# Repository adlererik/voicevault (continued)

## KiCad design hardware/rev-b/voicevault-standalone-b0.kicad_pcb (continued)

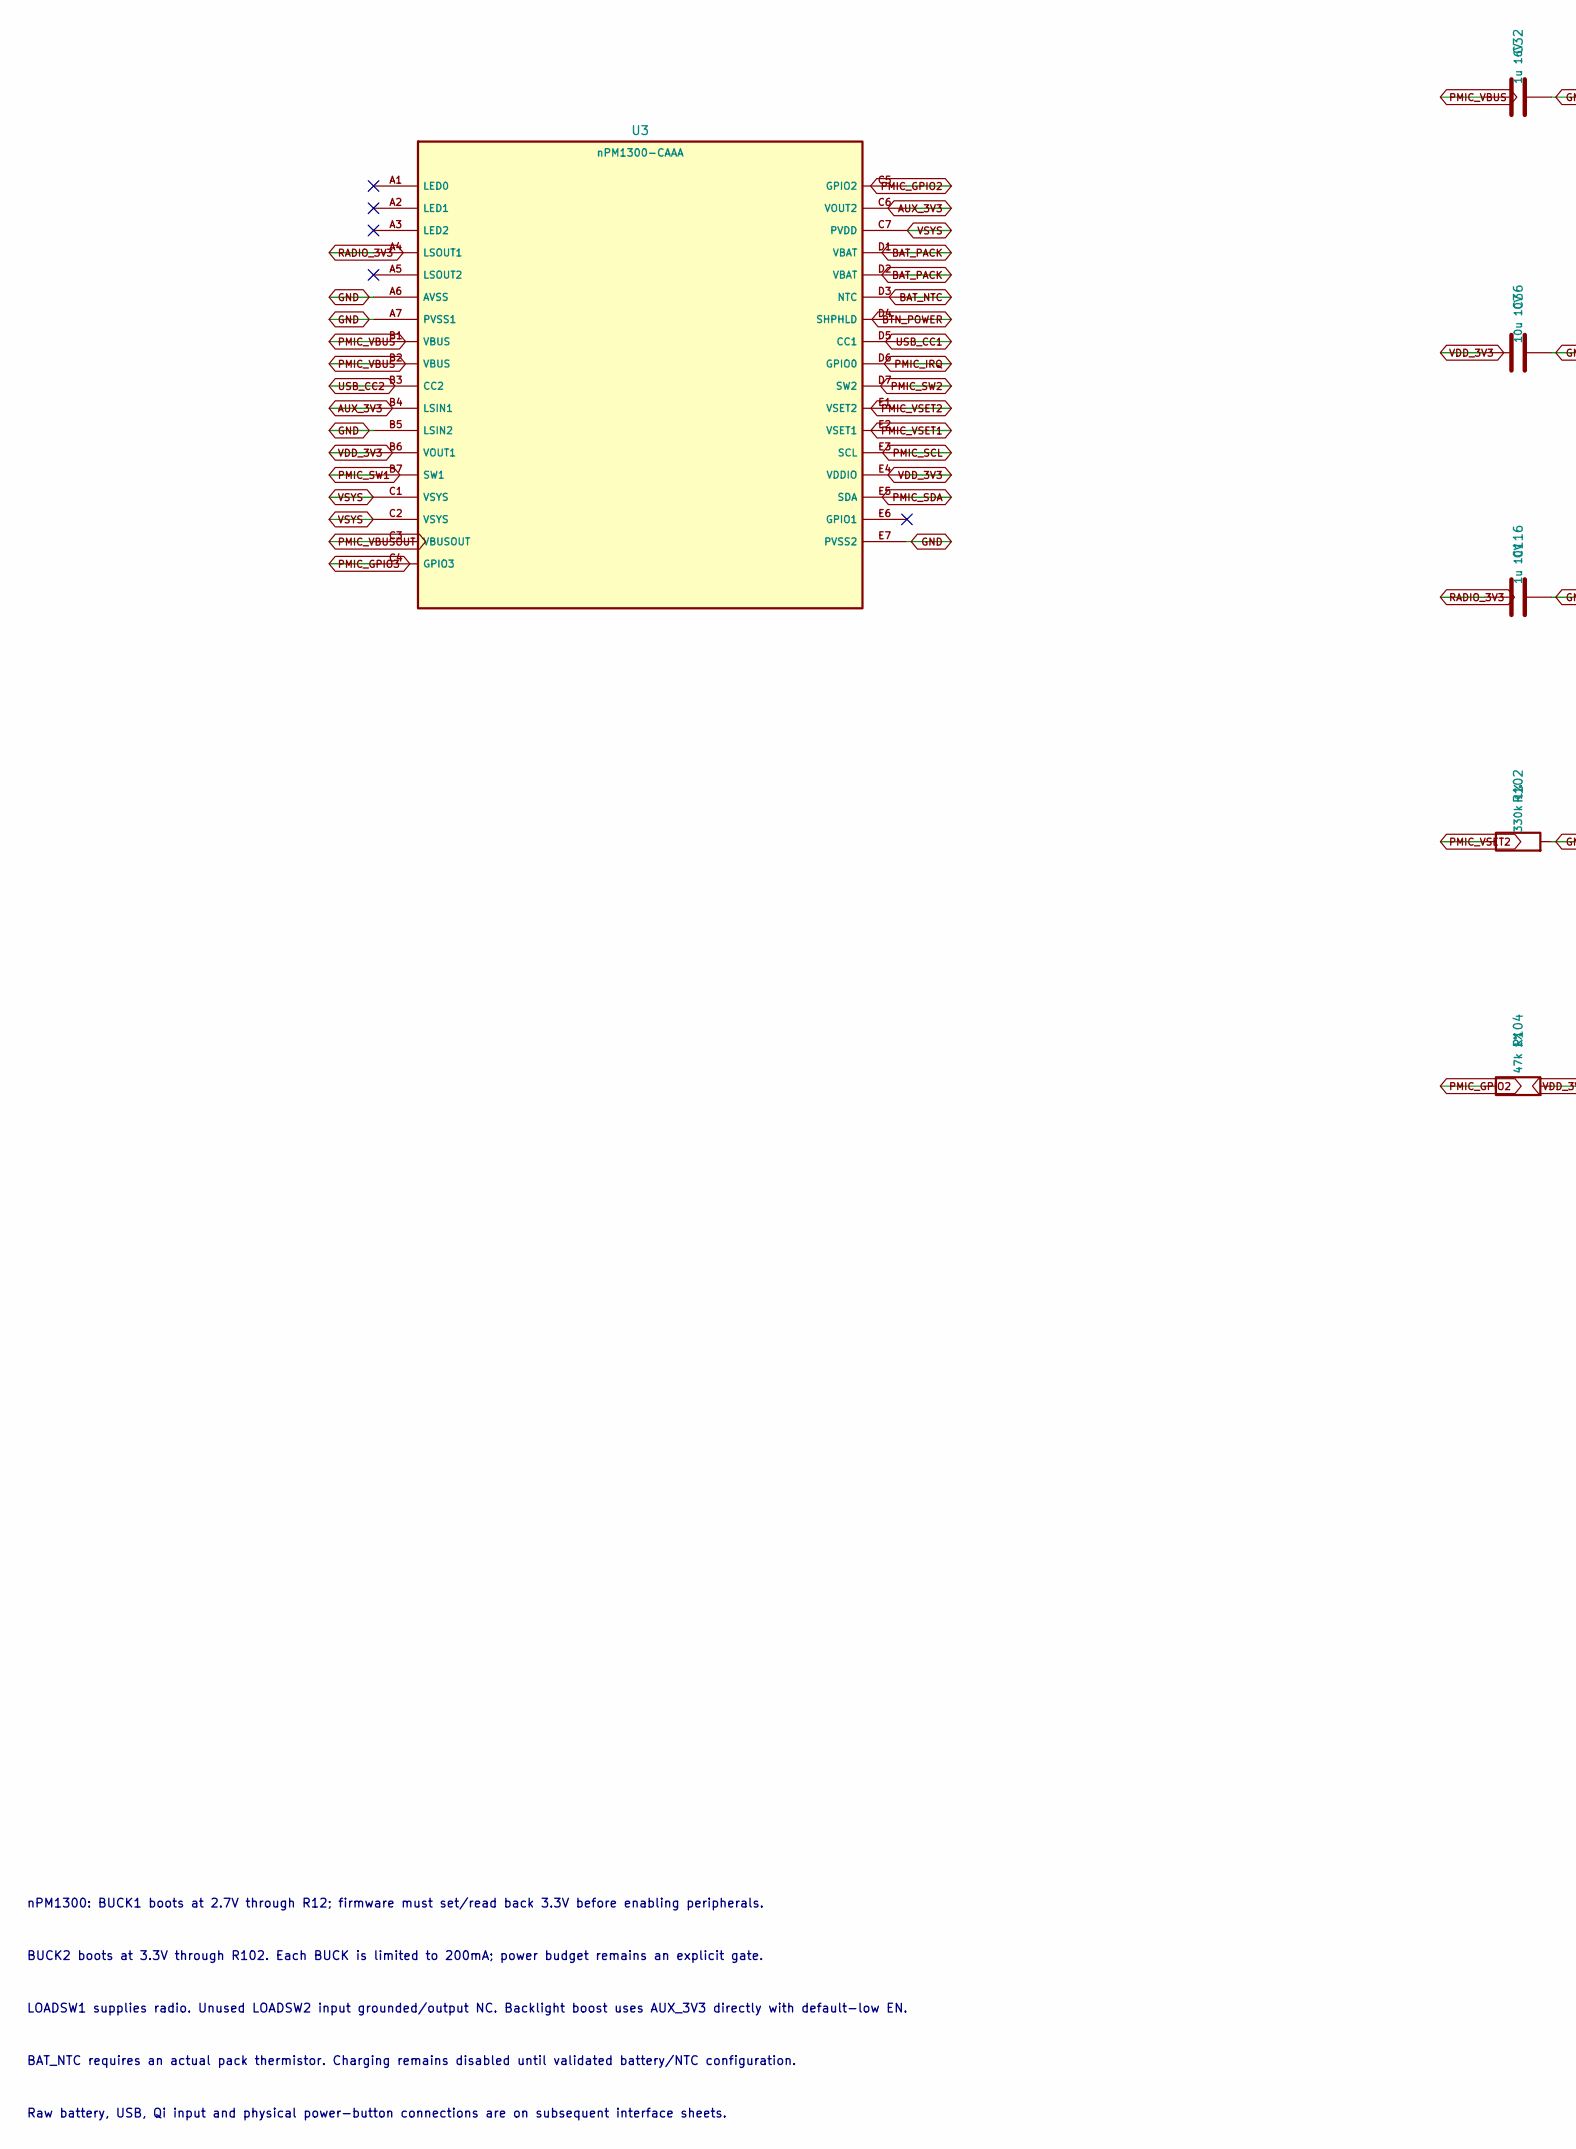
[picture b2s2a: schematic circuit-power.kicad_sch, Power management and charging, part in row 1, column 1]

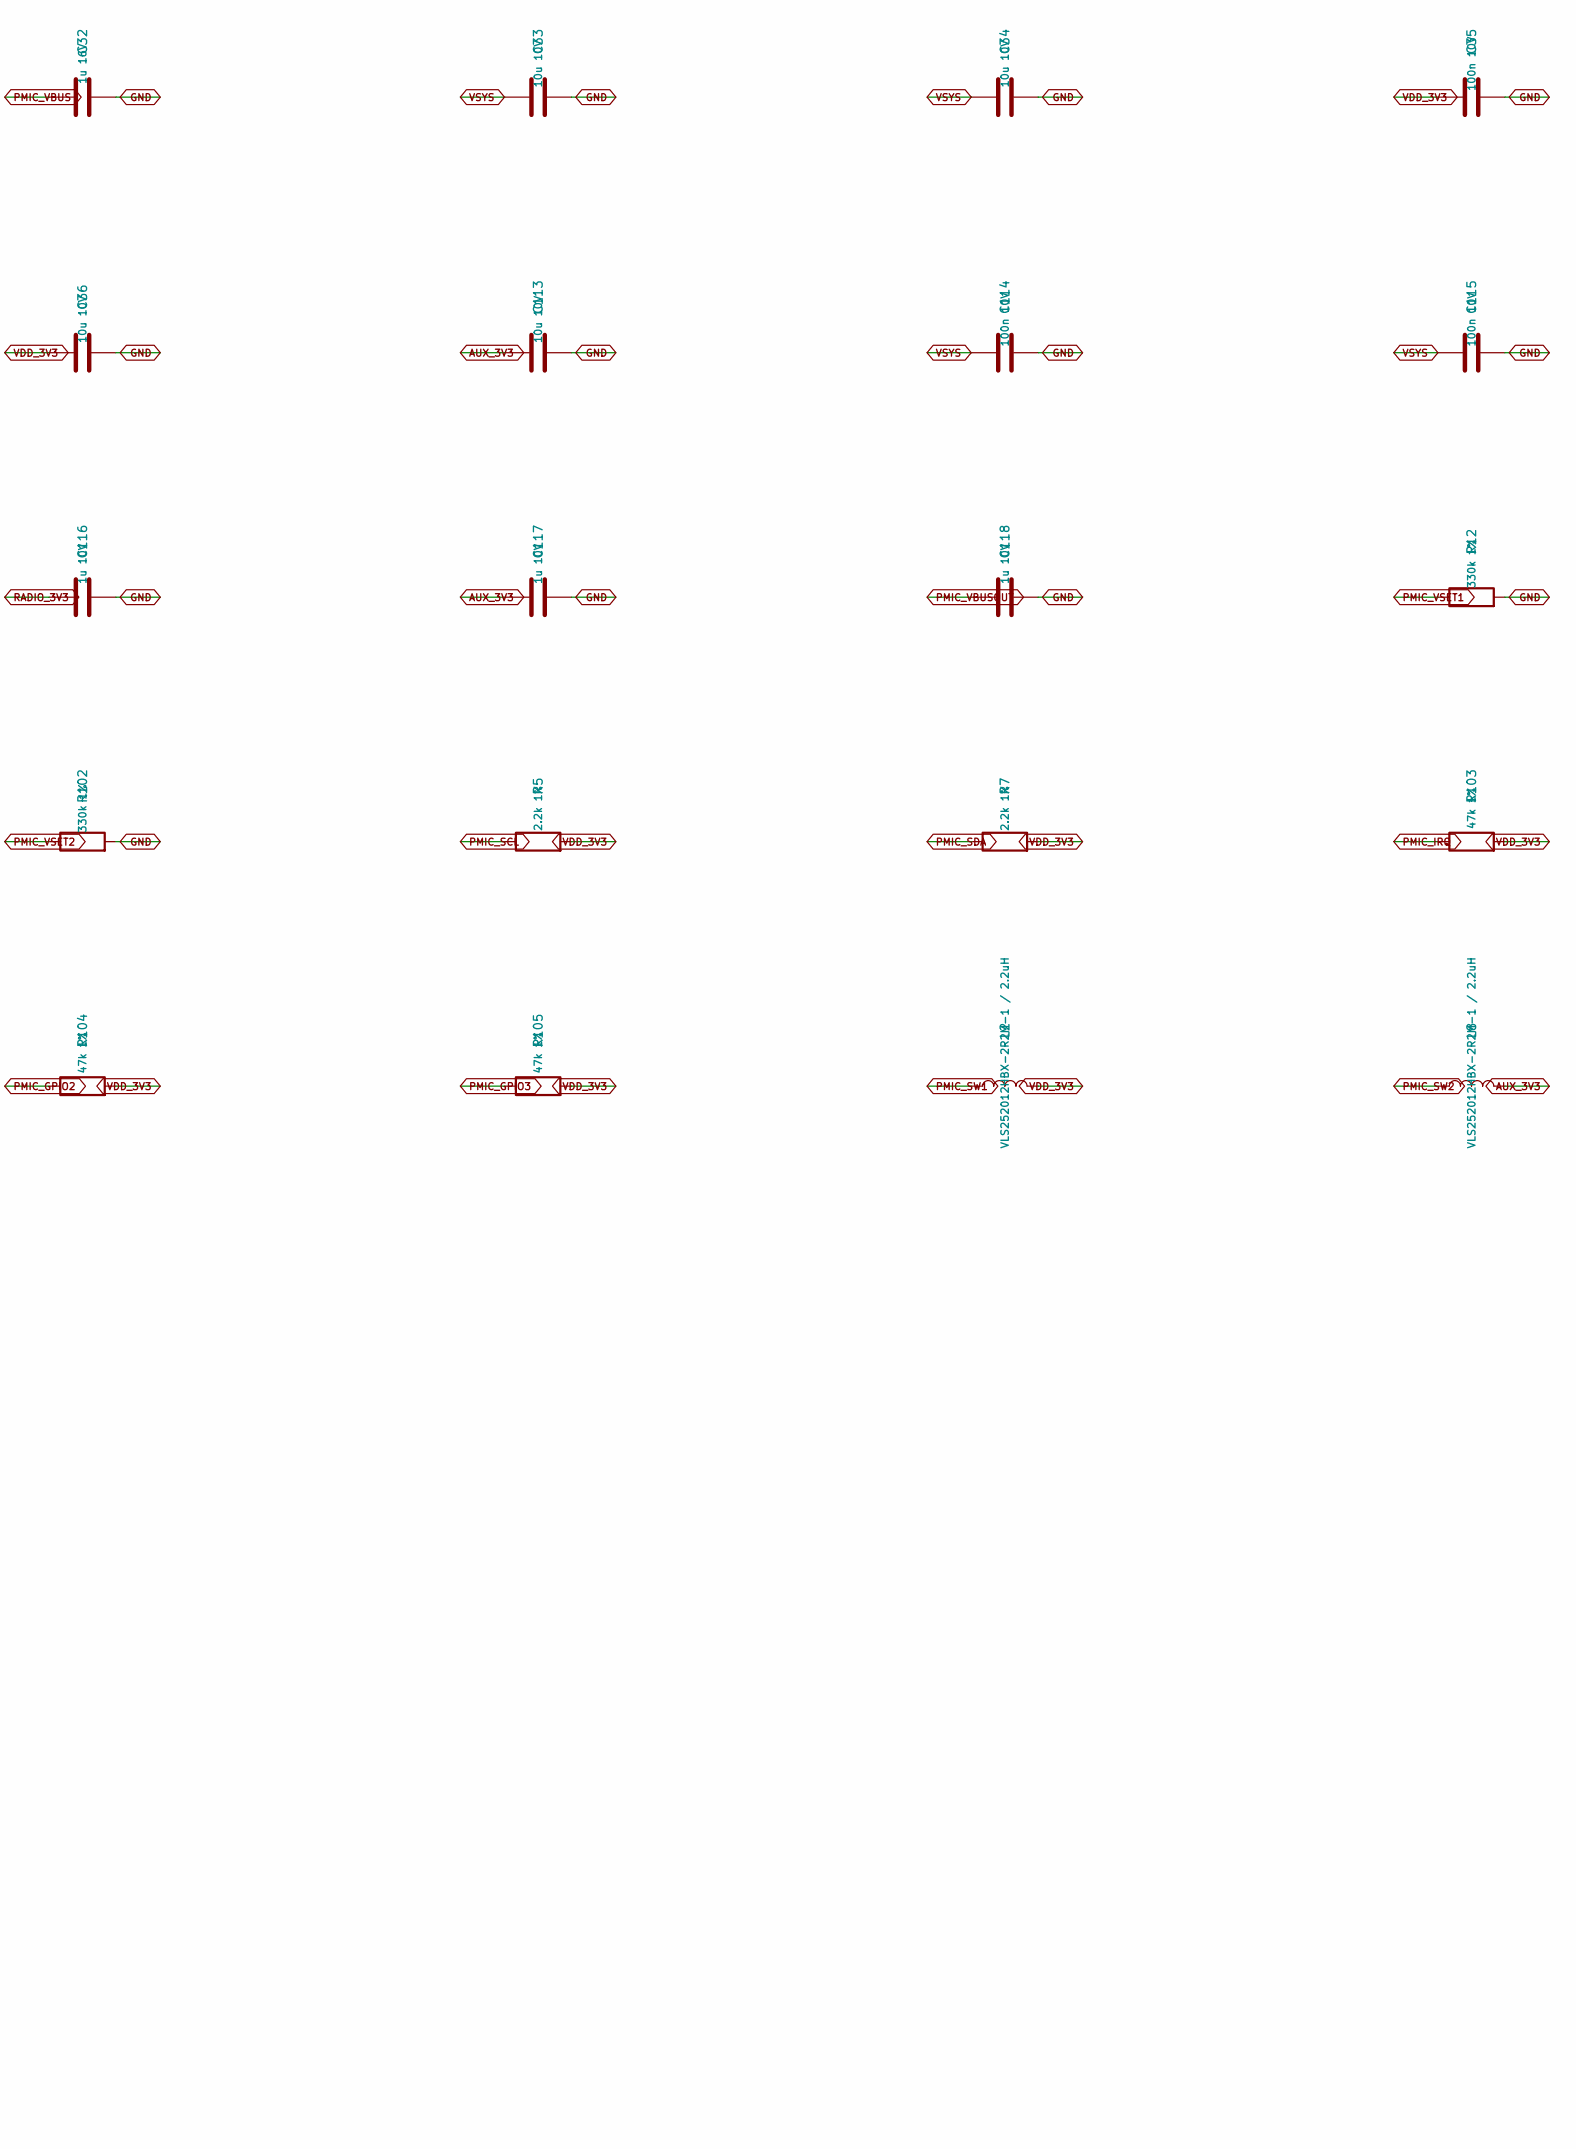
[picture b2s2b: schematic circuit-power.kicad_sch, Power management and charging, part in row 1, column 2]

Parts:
C32: 1u 16V; C_0603_1608Metric
C33, C34, C36, C113: 10u 10V; C_0603_1608Metric
C35, C114, C115: 100n 10V; C_0603_1608Metric
C116, C117, C118: 1u 10V; C_0603_1608Metric
L2, L8: VLS252012HBX-2R2M-1 / 2.2uH; L_1008_2520Metric
R5, R7: 2.2k 1%; R_0402_1005Metric
R12, R102: 330k 1%; R_0402_1005Metric
R103, R104, R105: 47k 1%; R_0402_1005Metric
U3: nPM1300-CAAA; nPM1300_CAAA_Nordic

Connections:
AUX_3V3: C113.1, C117.1, L8.2, U3.B4 (LSIN1), U3.C6 (VOUT2); also elsewhere on the board
BAT_NTC: U3.D3 (NTC); also elsewhere on the board
BAT_PACK: U3.D1 (VBAT), U3.D2 (VBAT); also elsewhere on the board
BTN_POWER: U3.D4 (SHPHLD); also elsewhere on the board
GND: C32.2, C33.2, C34.2, C35.2, C36.2, C113.2, C114.2, C115.2, C116.2, C117.2, C118.2, R12.2, R102.2, U3.A6 (AVSS), U3.A7 (PVSS1), U3.B5 (LSIN2), U3.E7 (PVSS2); also elsewhere on the board
PMIC_GPIO2: R104.1, U3.C5 (GPIO2); also elsewhere on the board
PMIC_GPIO3: R105.1, U3.C4 (GPIO3); also elsewhere on the board
PMIC_IRQ: R103.1, U3.D6 (GPIO0); also elsewhere on the board
PMIC_SCL: R5.1, U3.E3 (SCL); also elsewhere on the board
PMIC_SDA: R7.1, U3.E5 (SDA); also elsewhere on the board
PMIC_SW1: L2.1, U3.B7 (SW1)
PMIC_SW2: L8.1, U3.D7 (SW2)
PMIC_VBUS: C32.1, U3.B1 (VBUS), U3.B2 (VBUS); also elsewhere on the board
PMIC_VBUSOUT: C118.1, U3.C3 (VBUSOUT)
PMIC_VSET1: R12.1, U3.E2 (VSET1)
PMIC_VSET2: R102.1, U3.E1 (VSET2)
RADIO_3V3: C116.1, U3.A4 (LSOUT1); also elsewhere on the board
USB_CC1: U3.D5 (CC1); also elsewhere on the board
USB_CC2: U3.B3 (CC2); also elsewhere on the board
VDD_3V3: C35.1, C36.1, L2.2, R5.2, R7.2, R103.2, R104.2, R105.2, U3.B6 (VOUT1), U3.E4 (VDDIO); also elsewhere on the board
VSYS: C33.1, C34.1, C114.1, C115.1, U3.C1 (VSYS), U3.C2 (VSYS), U3.C7 (PVDD); also elsewhere on the board

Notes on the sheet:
nPM1300: BUCK1 boots at 2.7V through R12; firmware must set/read back 3.3V before enabling peripherals.
BUCK2 boots at 3.3V through R102. Each BUCK is limited to 200mA; power budget remains an explicit gate.
LOADSW1 supplies radio. Unused LOADSW2 input grounded/output NC. Backlight boost uses AUX_3V3 directly with default-low EN.
BAT_NTC requires an actual pack thermistor. Charging remains disabled until validated battery/NTC configuration.
Raw battery, USB, Qi input and physical power-button connections are on subsequent interface sheets.

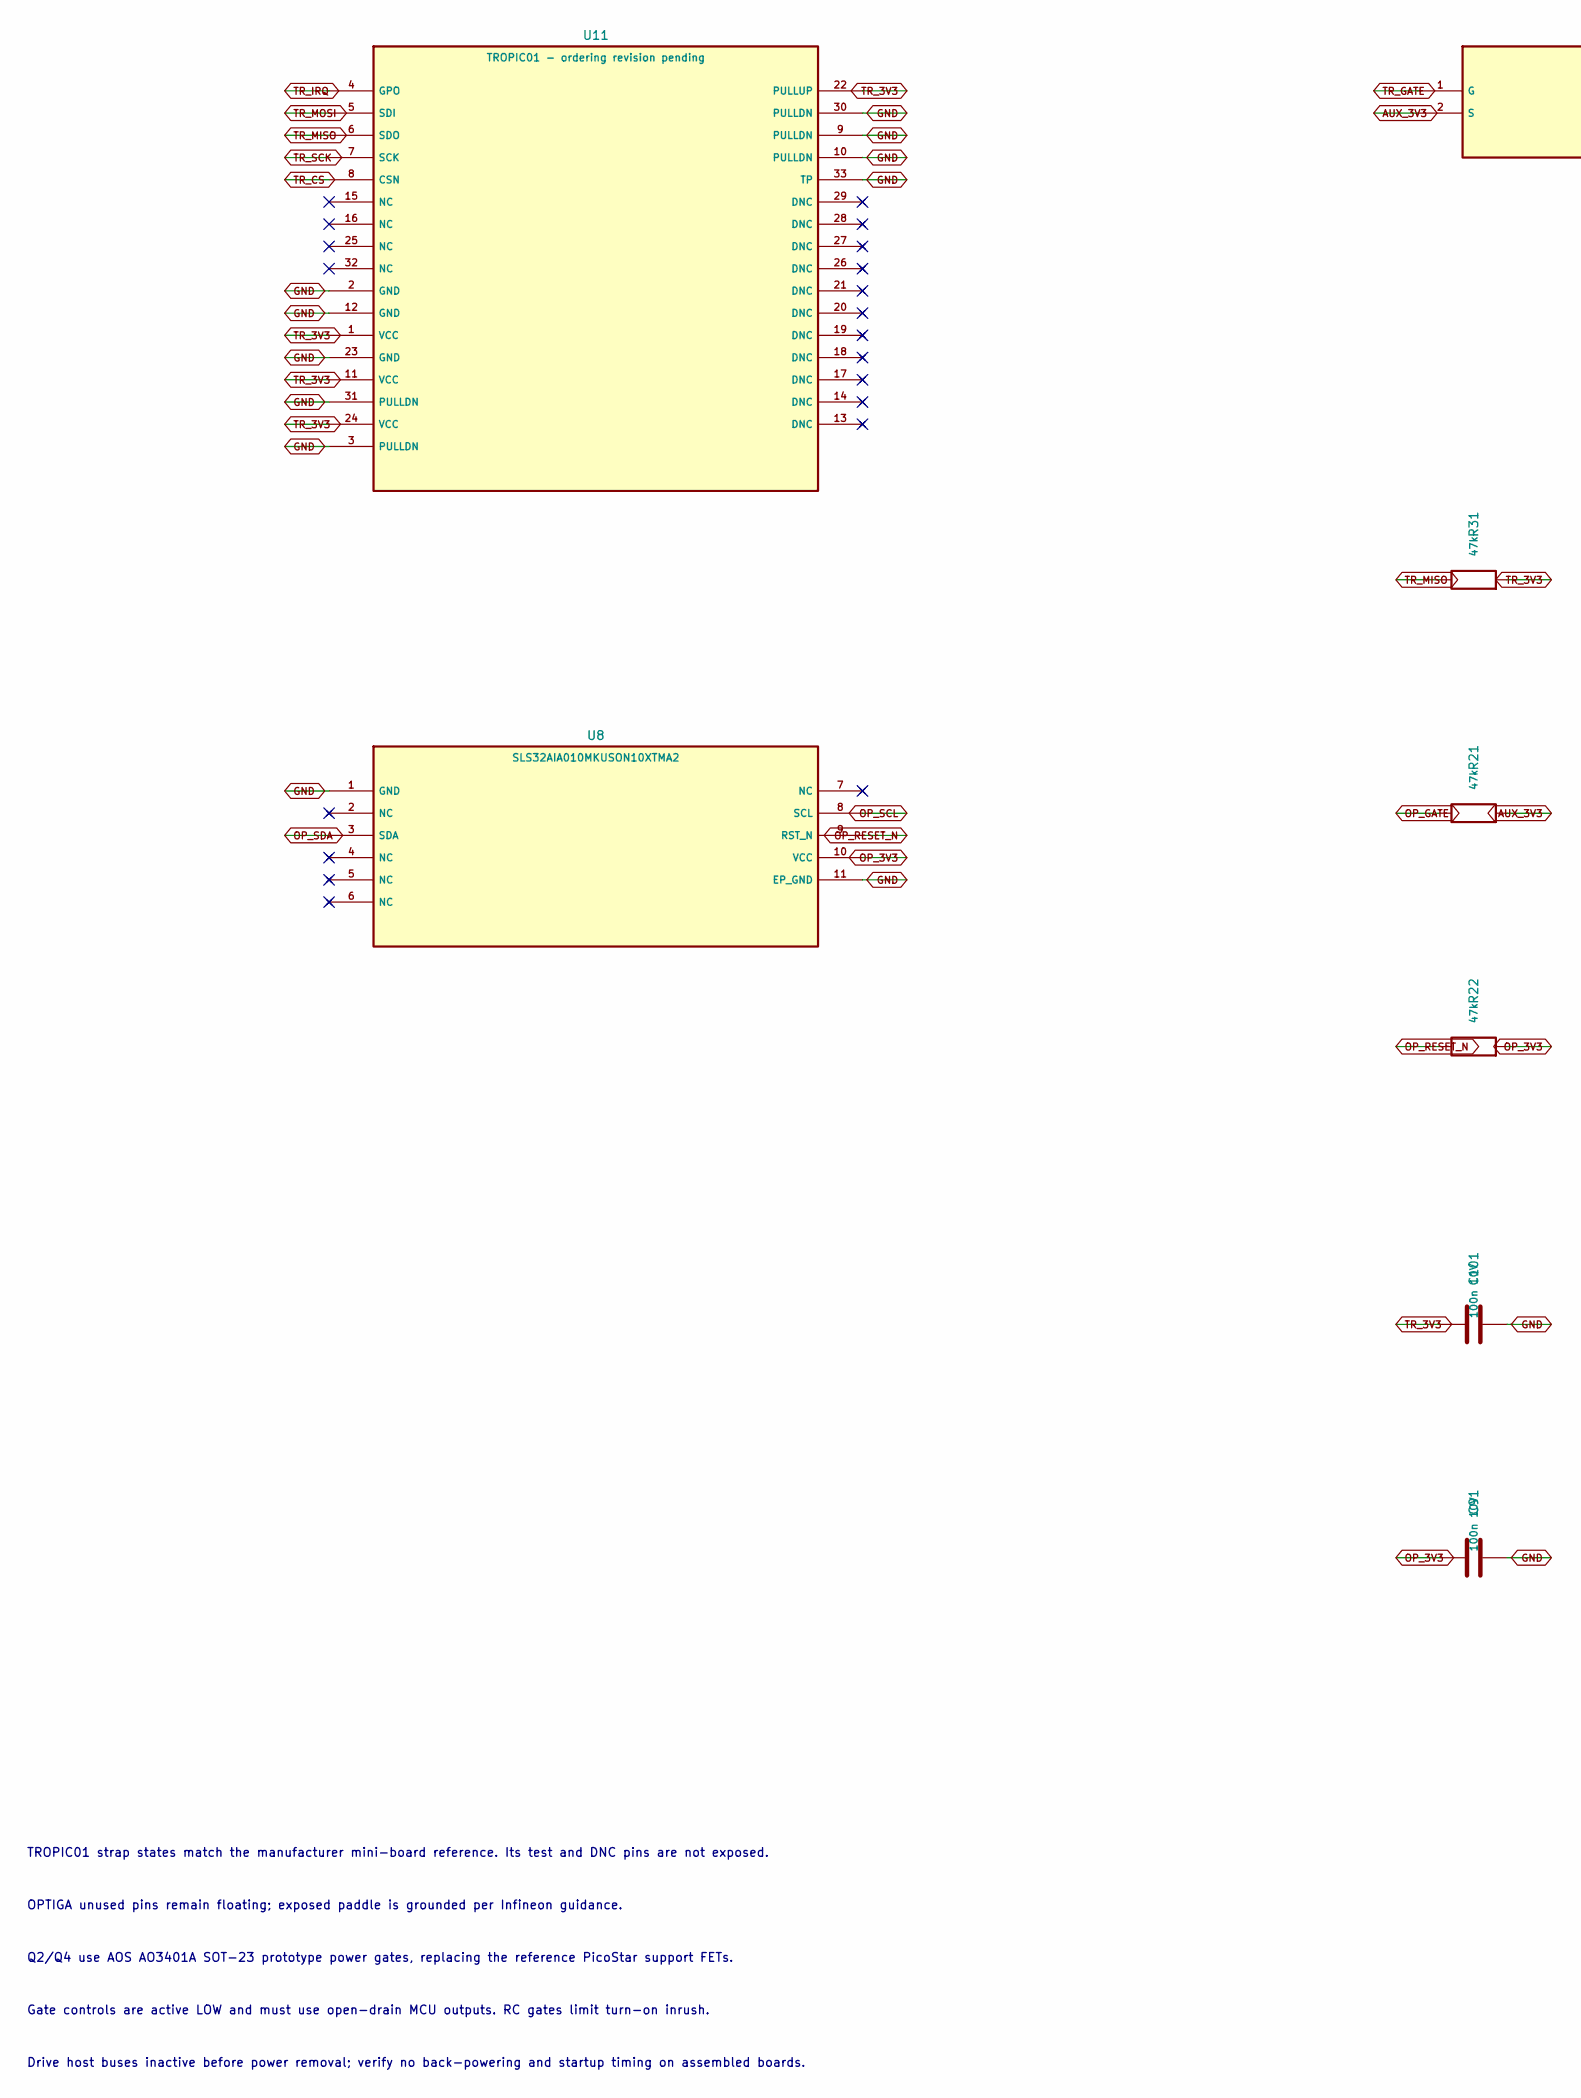
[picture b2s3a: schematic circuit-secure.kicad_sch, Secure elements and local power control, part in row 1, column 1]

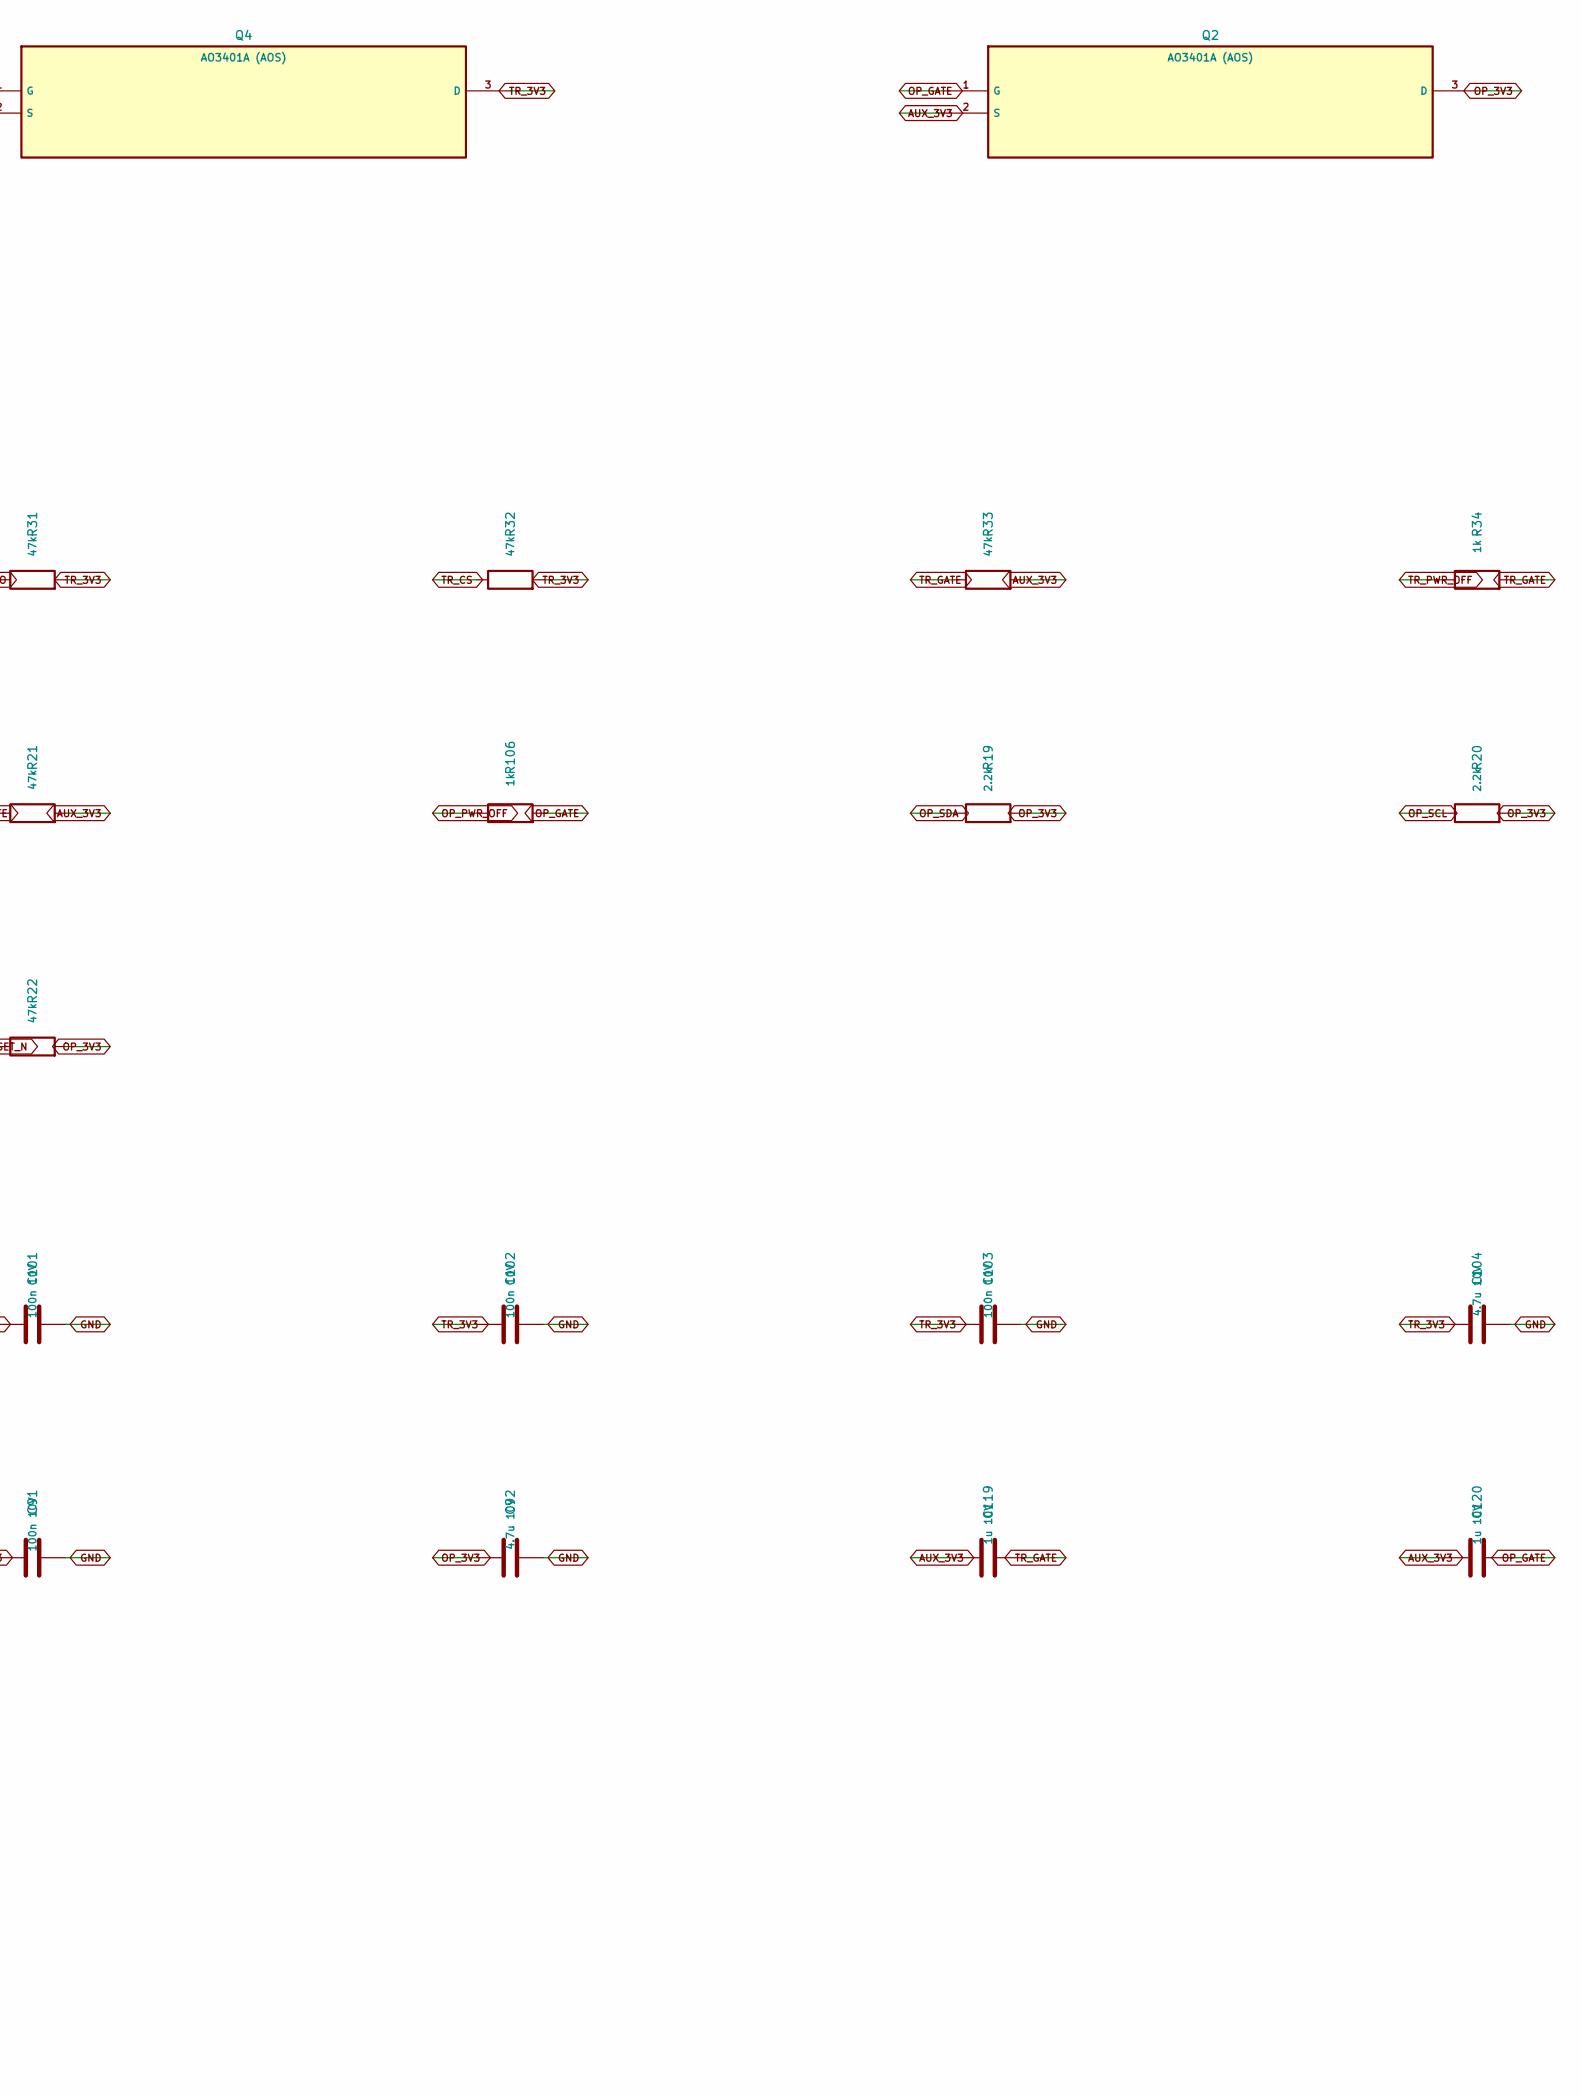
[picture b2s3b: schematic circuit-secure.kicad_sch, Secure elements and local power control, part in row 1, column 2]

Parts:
C91, C101, C102, C103: 100n 10V; C_0402_1005Metric
C92, C104: 4.7u 10V; C_0603_1608Metric
C119, C120: 1u 10V; C_0402_1005Metric
Q2, Q4: AO3401A (AOS); SOT-23
R19, R20: 2.2k; R_0402_1005Metric
R21, R22, R31, R32, R33: 47k; R_0402_1005Metric
R34, R106: 1k; R_0402_1005Metric
U8: SLS32AIA010MKUSON10XTMA2; OPTIGA_PG_USON10_2
U11: TROPIC01 - ordering revision pending; TROPIC01_QFN32_vendor

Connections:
AUX_3V3: C119.1, C120.1, Q2.2 (S), Q4.2 (S), R21.2, R33.2; also elsewhere on the board
GND: C91.2, C92.2, C101.2, C102.2, C103.2, C104.2, U8.1 (GND), U8.11 (EP_GND), U11.2 (GND), U11.3 (PULLDN), U11.9 (PULLDN), U11.10 (PULLDN), U11.12 (GND), U11.23 (GND), U11.30 (PULLDN), U11.31 (PULLDN), U11.33 (TP); also elsewhere on the board
OP_3V3: C91.1, C92.1, Q2.3 (D), R19.2, R20.2, R22.2, U8.10 (VCC); also elsewhere on the board
OP_GATE: C120.2, Q2.1 (G), R21.1, R106.2
OP_PWR_OFF: R106.1; also elsewhere on the board
OP_RESET_N: R22.1, U8.9 (RST_N); also elsewhere on the board
OP_SCL: R20.1, U8.8 (SCL); also elsewhere on the board
OP_SDA: R19.1, U8.3 (SDA); also elsewhere on the board
TR_3V3: C101.1, C102.1, C103.1, C104.1, Q4.3 (D), R31.2, R32.2, U11.1 (VCC), U11.11 (VCC), U11.22 (PULLUP), U11.24 (VCC); also elsewhere on the board
TR_CS: R32.1, U11.8 (CSN); also elsewhere on the board
TR_GATE: C119.2, Q4.1 (G), R33.1, R34.2
TR_IRQ: U11.4 (GPO); also elsewhere on the board
TR_MISO: R31.1, U11.6 (SDO); also elsewhere on the board
TR_MOSI: U11.5 (SDI); also elsewhere on the board
TR_PWR_OFF: R34.1; also elsewhere on the board
TR_SCK: U11.7 (SCK); also elsewhere on the board

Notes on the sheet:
TROPIC01 strap states match the manufacturer mini-board reference. Its test and DNC pins are not exposed.
OPTIGA unused pins remain floating; exposed paddle is grounded per Infineon guidance.
Q2/Q4 use AOS AO3401A SOT-23 prototype power gates, replacing the reference PicoStar support FETs.
Gate controls are active LOW and must use open-drain MCU outputs. RC gates limit turn-on inrush.
Drive host buses inactive before power removal; verify no back-powering and startup timing on assembled boards.
